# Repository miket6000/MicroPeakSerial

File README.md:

# MicroPeakSerial

The MicroPeakSerial is heavily based off the design detailed here [MicroPeakSerial](https://keithp.com/blogs/MicroPeakSerial/) by Keith Packard, but in KiCad rather than geda and including a housing designed in FreeCAD.

The only real changes are to include a USB A connector instead of the micro B to remove the need for a cable and to the footprint. A USB C connector was considered, but my prefered field laptop is old enough to not have one!

It should be noted that the current housing appears to hold the MicroPeak too far above the photo transistor for it to work effectively. I'm unsure at this point if I'll adjust the housing, or make improvements to the MicroPeakSerial by AC coupling the signal and using some positive feedback in the opamp to implement a basic bistable schmidt trigger. The latter option seems the better solution but brings a little complexity in ensuring the bistable opamp always powers up in the correct state.

TBC...

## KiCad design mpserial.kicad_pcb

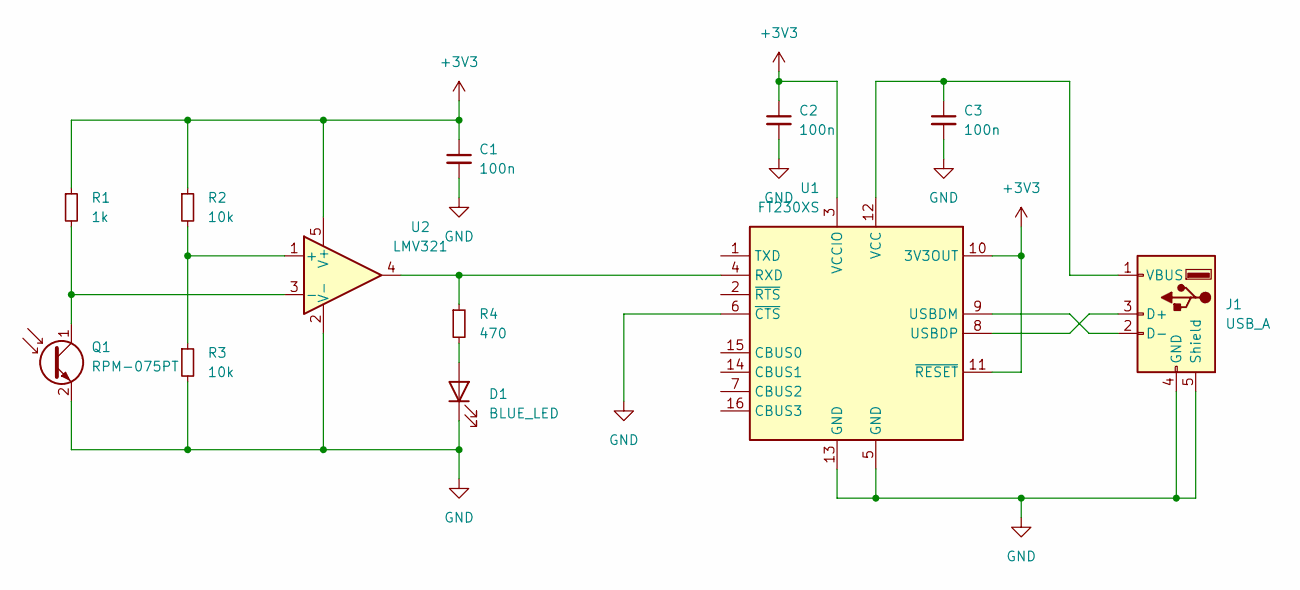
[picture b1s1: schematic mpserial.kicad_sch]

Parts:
C1, C2, C3: 100n; C_0402_1005Metric
D1: BLUE_LED; LED_0402_1005Metric
J1: USB_A; CONN_USB_A_MALE_HORIZONTAL_TH
Q1: RPM-075PT; LED_0805_2012Metric
R1: 1k; R_0402_1005Metric
R2, R3: 10k; R_0402_1005Metric
R4: 470; R_0402_1005Metric
U1: FT230XS; SSOP-16_3.9x4.9mm_P0.635mm
U2: LMV321; SOT-353_SC-70-5

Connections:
+3V3: C1.1, C2.1, R1.1, R2.1, U1.3 (VCCIO), U1.10 (3V3OUT), U1.11 (~RESET), U2.5 (V+)
GND: C1.2, C2.2, C3.2, D1.1 (K), J1.4 (GND), J1.5 (Shield), Q1.2 (E), R3.2, U1.5 (GND), U1.6 (~CTS), U1.13 (GND), U2.2 (V-)
unnamed: D1.2 (A), R4.2
unnamed: J1.3 (D+), U1.8 (USBDP)
unnamed: J1.2 (D-), U1.9 (USBDM)
unnamed: C3.1, J1.1 (VBUS), U1.12 (VCC)
unnamed: Q1.1 (C), R1.2, U2.3 (-)
unnamed: R4.1, U1.4 (RXD), U2.4
unnamed: R2.2, R3.1, U2.1 (+)

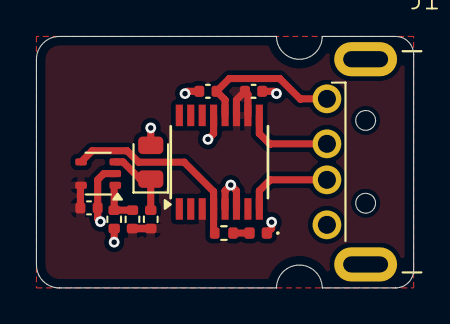
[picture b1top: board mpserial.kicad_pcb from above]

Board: 2 copper layers, 21.0 x 14.0 mm, 12 parts (0 on the bottom side), 9 nets.

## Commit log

2025-01-28 initial commit.
2025-02-05 corrected opamp footprint and symbol names, changed USB-A connector to throughhole for cheaper assembly
2025-02-24 Udated README with current project status
